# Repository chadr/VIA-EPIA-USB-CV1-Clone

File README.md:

# VIA EPIA USB CV1 clone
This is an open source clone of VIA's EPIA USB 1.1 Daughterboard USB-CV1. USB-CV1 is required to use the proprietary internal USB 1.1 header on some VIA EPIA motherboards like the EPIA-800AG.

## Why do I need this?
You can't just make an adapter cable to connect the VIA EPIA proprietary internal USB 1.1 header to a standard USB header cable. The internal EPIA header is directly connected to the raw output of the chipset south bridge. Doing so will fry your chipset in short order! And the ports will not work due to lack of bus termination and port enable signals.

For USB to work without damaging the chipset, you must provide the following:
* over voltage protection / transient protection
* over current protection
* power filtering / stiffening
* ESD protection
* bus termination
* EMI filtering / low-pass filter
* port enable signal

This clone of the USB-CV1 provides all of the above features.

## Bill of Materials
**Item**|**Qty**|**MFG Part Num**|**Mouser Part Num**
:-----:|:-----:|:-----:|:-----:
5.5V 30A Varistor|1|V5.5MLA0603NH|576-V5.5MLA0603NH
6V 2.6A Resettable Fuse|1|MINISMDC260F-2|650-MINISMDC260F-2
Ferrite Bead|1|-|-
ST USB 1.1 Bus IC|2|USBDF01W5|511-USBDF01W5
Wurth 1000uF 10V Cap|1|860020275015|710-860020275015
560K 1/8w Resistor|2|-|-
2x4 2.0mm female pin header|1|-|-
2x5 2.54mm male pin header|1|-|-

### Description and Function of Components
**5.5V 30A Varistor:** Protects +5V rail of motherboard from over voltage and transients. According to industry data, transients of up to +24V can be seen when hot plugging USB devices.  
**6V 2.6A Resettable Fuse:** Provides combined over current protection for both ports. USB 1.1 spec limits each port to 500mA for a combined rating of 1A for both ports. However, you must provide a 2.5x factor to allow for inrush current when hot plugging devices.  
**Ferrite Bead:** Filters high frequency digital noise (MHz range) from +5V rail. Any through hole ferrite bead that can handle > 2.5A will work fine here.  
**ST USB 1.1 Bus IC:** Provides ESD protection, bus termination, and EMI filtering (low pass filter) for USB 1.1 ports. Each chip handles one port, so two are required. Use of this reduces the component count by 20 compared to VIA's discrete design.  
**Wurth 1000uF 10V Cap:** Provides stiffening for the +5V rail when hot plugging devices cause an inrush. This is bulk capacitance only. It does not filter. There is no benefit to using a more expensive low ESR cap in this application. Any cheap electrolytic with a voltage rating > 10V will work fine.  
**560K 1/8w Resistor:** Pullup resistors for the port enable pins on the motherboard chipset. The value here is not that critical. I only used 560K because that's what VIA used on their original design. But I'd bet that anything from 100K to 560K would work just fine. Can be 1%, 5%, metal film, carbon, whatever.  

## PCB Info
4 Layer  
1.2mm thickness  
32mm by 20mm  
HASL is fine. Paying extra for ENIG will not improve anything in this application.

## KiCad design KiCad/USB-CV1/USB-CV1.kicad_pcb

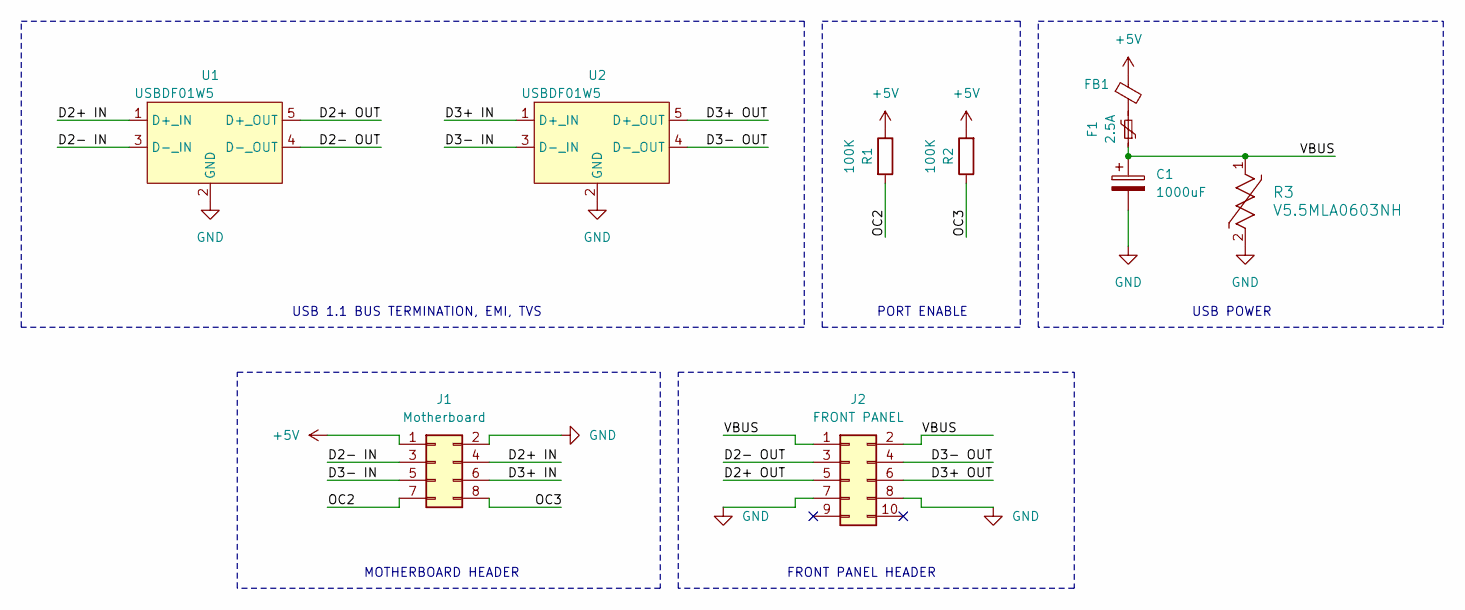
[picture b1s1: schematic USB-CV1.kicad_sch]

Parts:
C1: 1000uF; CP_Radial_D8.0mm_P5.00mm
F1: 2.5A; R_1812_4532Metric_Pad1.30x3.40mm_HandSolder
FB1: R_Axial_DIN0411_L9.9mm_D3.6mm_P12.70mm_Horizontal
J1: Motherboard; PinHeader_2x04_P2.00mm_Vertical
J2: FRONT PANEL; PinHeader_2x05_P2.54mm_Vertical
R1, R2: 100K; R_Axial_DIN0204_L3.6mm_D1.6mm_P5.08mm_Horizontal
R3: V5.5MLA0603NH; VRES_MLA-0603_LTF
U1, U2: USBDF01W5; SOT323-5L_STM-M

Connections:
+5V: FB1.1, J1.1, R1.1, R2.2
/D2+ IN: J1.4, U1.1 (D+_IN)
/D2+ OUT: J2.5, U1.5 (D+_OUT)
/D2- IN: J1.3, U1.3 (D-_IN)
/D2- OUT: J2.3, U1.4 (D-_OUT)
/D3+ IN: J1.6, U2.1 (D+_IN)
/D3+ OUT: J2.6, U2.5 (D+_OUT)
/D3- IN: J1.5, U2.3 (D-_IN)
/D3- OUT: J2.4, U2.4 (D-_OUT)
/OC2: J1.7, R1.2
/OC3: J1.8, R2.1
/VBUS: C1.1, F1.1, J2.1, J2.2, R3.1
GND: C1.2, J1.2, J2.7, J2.8, R3.2, U1.2 (GND), U2.2 (GND)
unnamed: F1.2, FB1.2

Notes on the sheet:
MOTHERBOARD HEADER
FRONT PANEL HEADER
USB POWER
PORT ENABLE
USB 1.1 BUS TERMINATION, EMI, TVS

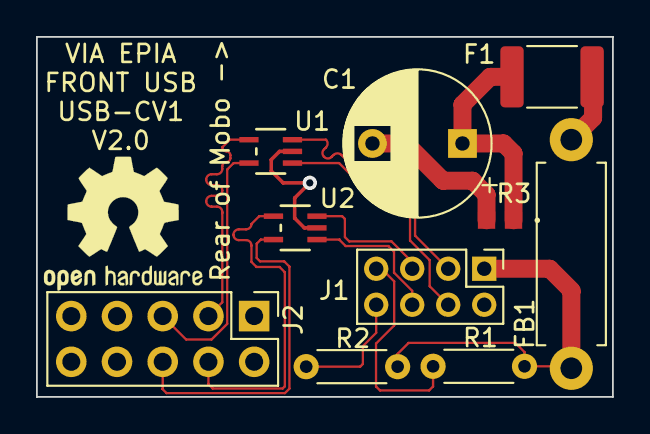
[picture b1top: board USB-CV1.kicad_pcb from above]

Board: 4 copper layers, 32.0 x 20.0 mm, 10 parts (0 on the bottom side), 14 nets.

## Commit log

2024-01-05 clean up file structure
2024-01-05 file clean up
2024-01-05 update pcb text
